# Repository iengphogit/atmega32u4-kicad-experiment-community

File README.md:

# ATmega32U4 Arduino-Compatible USB-C Bluetooth Module

This KiCad project is a learning-focused starter design for an ATmega32U4-based Arduino-compatible module. It includes a schematic-first design flow, a PCB layout with placed footprints, a custom module footprint example, and notes for using KiCad MCP automation.

## Repository Scope

This repository contains KiCad project files, learning notes, and usage examples
for KiCad MCP. It does not vendor or mirror the full `kicad-mcp` npm package
source code.

For the KiCad MCP source code, package launcher, Codex skill, and KiCad action
plugin implementation, use:

```text
https://github.com/iengphogit/kicad-mcp
```

## What This Project Contains

- ATmega32U4 microcontroller schematic connectivity
- USB Type-C female connector wiring
- HC-05 / HM-10 compatible Bluetooth header
- Arduino-style 2.54 mm headers
- Reset circuit
- 16 MHz crystal circuit
- USB-C CC1/CC2 5.1k pull-down support
- Power and decoupling capacitors
- PCB footprints placed in PCB Editor
- Rectangular board outline on `Edge.Cuts`
- Custom example footprint library in `TestDemo.pretty`

## Included KiCad Projects

This community repo now contains multiple KiCad learning projects:

- `TestDemo.kicad_pro` - ATmega32U4 Arduino-compatible USB-C Bluetooth module
- `Card_Reader_Adapter/Card_Reader_Adapter.kicad_pro` - smart-card reader adapter with ISO 7816 contacts and RJ45 connector

## Project Files

```text
TestDemo.kicad_pro     KiCad project file
TestDemo.kicad_sch     Main schematic
TestDemo.kicad_pcb     PCB layout
fp-lib-table           Project footprint library table
TestDemo.pretty/       Project-local footprint library
KICAD_STARTUP_SCENARIO.md  Learning notes and startup scenario
```

Generated reports:

```text
TestDemo.erc.json          ERC report for schematic
TestDemo.validate-drc.json DRC report for PCB
```

Backup files are also present because KiCad MCP write operations were run with backups enabled.

## Recommended Learning Order

Start with **Schematic Editor**, not Footprint Editor.

1. Open the KiCad project.
2. Learn symbols, wires, labels, and nets in Schematic Editor.
3. Assign footprints to schematic symbols.
4. Update PCB from schematic.
5. Place and route footprints in PCB Editor.
6. Use Footprint Editor only when creating or editing one reusable physical footprint.
7. Run ERC and DRC before manufacturing output.

Important distinction:

```text
Symbol          Electrical part in schematic
Footprint       Physical pad pattern for one part
Net             Named electrical connection
PCB layout      Physical board with placed footprints and routed tracks
```

## Opening The Project In KiCad

1. Install KiCad 9.x or newer.
2. Open KiCad.
3. Open this project file:

```text
TestDemo.kicad_pro
```

From the Project Manager:

- Open **Schematic Editor** to see the ATmega32U4 circuit.
- Open **PCB Editor** to see the placed PCB footprints and board outline.
- Open **Footprint Editor** only to inspect project-local custom footprints.

## Viewing The Schematic

Open:

```text
TestDemo.kicad_sch
```

The schematic includes:

- `U1`: ATmega32U4-A
- `J1`: USB-C receptacle
- `J2`: Arduino-compatible digital header
- `J3`: power, analog, and USB breakout header
- `J4`: HC-05 / HM-10 Bluetooth header
- `R1`, `R2`: 5.1k USB-C CC pull-down resistors
- `R3`: reset pull-up
- `SW1`: reset switch
- `Y1`: 16 MHz crystal
- `C1` to `C8`: decoupling, UCAP, AREF, 5V bulk, and crystal load capacitors

Key net labels:

```text
5V
VCC
GND
RESET
USB_DP
USB_DM
CC1
CC2
TX0
RX1
D2_SDA
D3_SCL
D4 to D10
A0 to A5
BT_STATE
BT_EN_KEY
```

## Viewing The PCB

Open:

```text
TestDemo.kicad_pcb
```

The PCB contains placed footprints for:

- ATmega32U4 TQFP-44
- USB-C connector
- Digital, analog, power, USB, and Bluetooth headers
- Resistors and capacitors
- Crystal
- Reset switch
- Four M2 mounting holes
- Board outline on `Edge.Cuts`

If footprints are visible in PCB Editor but not in Footprint Editor, that is normal. PCB Editor shows the board. Footprint Editor shows only one reusable footprint from a library.

## Viewing The Custom Footprint

This project also includes a project-local footprint library:

```text
TestDemo.pretty/
```

It is registered by:

```text
fp-lib-table
```

The custom footprint file is:

```text
TestDemo.pretty/ATmega32U4_Arduino_USB-C_BT_Module.kicad_mod
```

To view it in Footprint Editor:

1. Open `TestDemo.kicad_pro` in KiCad.
2. Open **Footprint Editor**.
3. Select the `TestDemo` library from the library tree.
4. Open `ATmega32U4_Arduino_USB-C_BT_Module`.

If the Footprint Editor appears empty, make sure the project was opened from `TestDemo.kicad_pro`, not by opening a single `.kicad_mod` file directly.

## USB-C Connectivity

The schematic uses these USB-C connections:

```text
VBUS   -> 5V
GND    -> GND
Shield -> GND
D+     -> USB_DP
D-     -> USB_DM
CC1    -> 5.1k pull-down to GND
CC2    -> 5.1k pull-down to GND
SBU1   -> no connect
SBU2   -> no connect
```

## Bluetooth Header

The Bluetooth header is intended for HC-05 / HM-10 style modules:

```text
Pin 1  VCC
Pin 2  GND
Pin 3  RX1
Pin 4  TX0
Pin 5  BT_STATE
Pin 6  BT_EN_KEY
```

Check the exact TX/RX direction for your module before manufacturing. Many Bluetooth modules label pins from the module perspective, so MCU `TX0` normally connects to module `RX`, and MCU `RX1` normally connects to module `TX`.

## KiCad Checks

Run ERC from KiCad:

```text
Schematic Editor > Inspect > Electrical Rules Checker
```

Run DRC from KiCad:

```text
PCB Editor > Inspect > Design Rules Checker
```

Command-line examples on macOS with KiCad installed in `/Applications`:

```sh
/Applications/KiCad/KiCad.app/Contents/MacOS/kicad-cli sch erc \
  --output TestDemo.erc.json \
  --format json \
  TestDemo.kicad_sch

/Applications/KiCad/KiCad.app/Contents/MacOS/kicad-cli pcb drc \
  --output TestDemo.validate-drc.json \
  --format json \
  TestDemo.kicad_pcb
```

## Update PCB From Schematic

After editing the schematic, update the PCB from KiCad GUI:

```text
PCB Editor > Tools > Update PCB from Schematic
```

This step synchronizes footprints, nets, and ratsnest connections from the schematic into the PCB.

Note: the installed `kicad-cli` can run ERC, DRC, exports, and reports, but it does not expose full GUI-equivalent **Update PCB from Schematic** for this setup. Use the KiCad GUI for that step.

## Install KiCad MCP With npm

KiCad MCP lets AI tools inspect and automate KiCad projects. The npm package provides a Node.js launcher for the KiCad MCP server.

Requirements:

- Node.js and npm
- Python 3.10 or newer
- KiCad installed
- `kicad-cli` available or passed with `--kicad-cli`

Check npm package information:

```sh
npm view kicad-mcp version description bin
```

Run KiCad MCP directly with `npx`:

```sh
npx -y kicad-mcp@latest
```

By default this runs MCP over stdio, which is the normal mode for MCP clients.

Run setup explicitly:

```sh
npx -y kicad-mcp@latest --setup
```

Run local HTTP mode:

```sh
npx -y kicad-mcp@latest --http --host 127.0.0.1 --port 8765
```

The HTTP MCP endpoint is:

```text
http://127.0.0.1:8765/mcp
```

Keep the host set to `127.0.0.1` unless you add proper authentication.

Install globally with npm:

```sh
npm install -g kicad-mcp
```

Then run:

```sh
kicad-mcp --help
kicad-mcp --stdio
kicad-mcp --http --host 127.0.0.1 --port 8765
```

Useful options:

```sh
kicad-mcp --setup
kicad-mcp --install-codex-skill
kicad-mcp --python /path/to/python3
kicad-mcp --venv /path/to/venv
kicad-mcp --kicad-cli /Applications/KiCad/KiCad.app/Contents/MacOS/kicad-cli
```

## MCP Client Configuration

Example MCP client configuration using `npx`:

```json
{
  "mcpServers": {
    "kicad": {
      "command": "npx",
      "args": ["-y", "kicad-mcp@latest"]
    }
  }
}
```

Example HTTP startup command:

```sh
npx -y kicad-mcp@latest --http --host 127.0.0.1 --port 8765 \
  --kicad-cli /Applications/KiCad/KiCad.app/Contents/MacOS/kicad-cli
```

## Install The Codex Skill

The npm package can install the bundled Codex skill:

```sh
npx -y kicad-mcp@latest --install-codex-skill
```

This installs the skill to:

```text
~/.codex/skills/kicad-mcp
```

If Codex uses a custom home directory, install to that directory instead:

```sh
CODEX_HOME="/path/to/codex-home" npx -y kicad-mcp@latest --install-codex-skill
```

Use the actual Codex home directory for your environment as `CODEX_HOME`.

After restarting Codex, use:

```text
$kicad-mcp
```

Run Codex from this repository root so the skill can inspect `TestDemo.kicad_pro`, `TestDemo.kicad_sch`, and `TestDemo.kicad_pcb`.

Example prompt:

```text
Use $kicad-mcp to inspect this KiCad project, run ERC/DRC, and report the current schematic and board status.
```

## KiCad MCP Safe Workflow

Recommended automation order:

1. Find project files: `.kicad_pro`, `.kicad_sch`, `.kicad_pcb`.
2. Run read-only checks first: project summary, schematic statistics, board statistics.
3. Before write operations, run `dry_run=true` when supported.
4. Keep `create_backup=true` for edits.
5. After schematic edits, run ERC.
6. After PCB edits, run DRC.
7. Report changed files, generated reports, and backup paths.

Useful KiCad MCP task examples:

```text
kicad_find_project_files
kicad_project_summary
kicad_schematic_statistics
kicad_list_schematic_symbols
kicad_list_schematic_nets
kicad_run_erc
kicad_board_statistics
kicad_list_board_footprints
kicad_validate_board
kicad_run_drc
kicad_export_bom
kicad_export_gerbers
kicad_export_drill_files
```

## KiCad GUI Bridge

Some KiCad MCP GUI actions require the PCB Editor bridge.

To use it:

1. Open KiCad PCB Editor.
2. Open the target board.
3. Run:

```text
Tools > External Plugins > KiCad AI MCP
```

The GUI bridge normally listens locally at:

```text
http://127.0.0.1:8766/status
```

If the bridge is not running, MCP can still edit saved KiCad files, but live GUI actions such as selecting, zooming, and moving visible PCB items will not work.

## Suggested Beginner Workflow For This Project

1. Open `TestDemo.kicad_pro`.
2. Open Schematic Editor and study the net labels.
3. Run ERC.
4. Open PCB Editor.
5. Run **Update PCB from Schematic**.
6. Inspect the placed footprints.
7. Route `USB_DP` and `USB_DM` carefully as a short pair.
8. Route power and ground.
9. Add a ground zone.
10. Run DRC.
11. Generate fabrication outputs only after DRC is clean.

## Manufacturing Outputs

When the board is ready, generate files from PCB Editor:

```text
File > Fabrication Outputs > Gerbers
File > Fabrication Outputs > Drill Files
File > Fabrication Outputs > Component Placement
```

You can also use KiCad MCP or `kicad-cli` for exports after the board is finalized.

## Notes

- This is a starter learning design, not a certified Arduino product.
- Review the ATmega32U4 datasheet before manufacturing.
- Confirm USB-C footprint compatibility with the exact connector part number.
- Confirm Bluetooth module pin direction and voltage level requirements.
- Route USB data lines carefully and keep them short.
- Add or tune PCB design rules before ordering boards.

## Credits And Contact

Created by Ieng Pho.

- GitHub: [iengphogit](https://github.com/iengphogit)
- Facebook: [ieng.pho](https://www.facebook.com/ieng.pho/)
- LinkedIn: [Ieng Pho](https://www.linkedin.com/in/ieng-pho-7a4328189/)
- Email: [iengpho@gmail.com](mailto:iengpho@gmail.com)

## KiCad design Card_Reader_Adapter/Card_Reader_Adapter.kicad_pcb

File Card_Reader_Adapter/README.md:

# Card Reader Adapter KiCad Project

KiCad project for a smart-card reader adapter inspired by `nkinder/smart-card-removinator`.

The PCB uses ISO 7816 contact pads on the card-reader side and an RJ45 connector on the cable side. The routed core nets are:

- RJ45 pin 1 -> AUX1
- RJ45 pin 2 -> I/O
- RJ45 pin 3 -> CLK
- RJ45 pin 4 -> AUX2
- RJ45 pin 5 -> RST
- RJ45 pin 6 -> VPP
- RJ45 pin 7 -> GND
- RJ45 pin 8 -> VCC

Important fabrication note: order this board as **0.031 inch / 0.8 mm PCB thickness** so it can fit into a smart-card reader slot.

Files:

- `Card_Reader_Adapter.kicad_pro` - KiCad project
- `Card_Reader_Adapter.kicad_sch` - visible schematic with U1 smart-card contacts and J1 RJ45 mapping
- `Card_Reader_Adapter.kicad_sym` / `sym-lib-table` - project-local schematic symbols
- `Card_Reader_Adapter.kicad_pcb` - routed PCB layout
- `Card_Reader_Adapter.pretty/` - project-local footprints
- `reference/` - original SVG schematic and Gerber files from the public reference repository

Validation run with KiCad 9.0.4:

- ERC: 0 violations
- DRC: 0 violations, 0 unconnected items

R1 is included as an optional RJ45 LED resistor footprint. The smart-card adapter core is the eight ISO 7816 signal routes listed above.

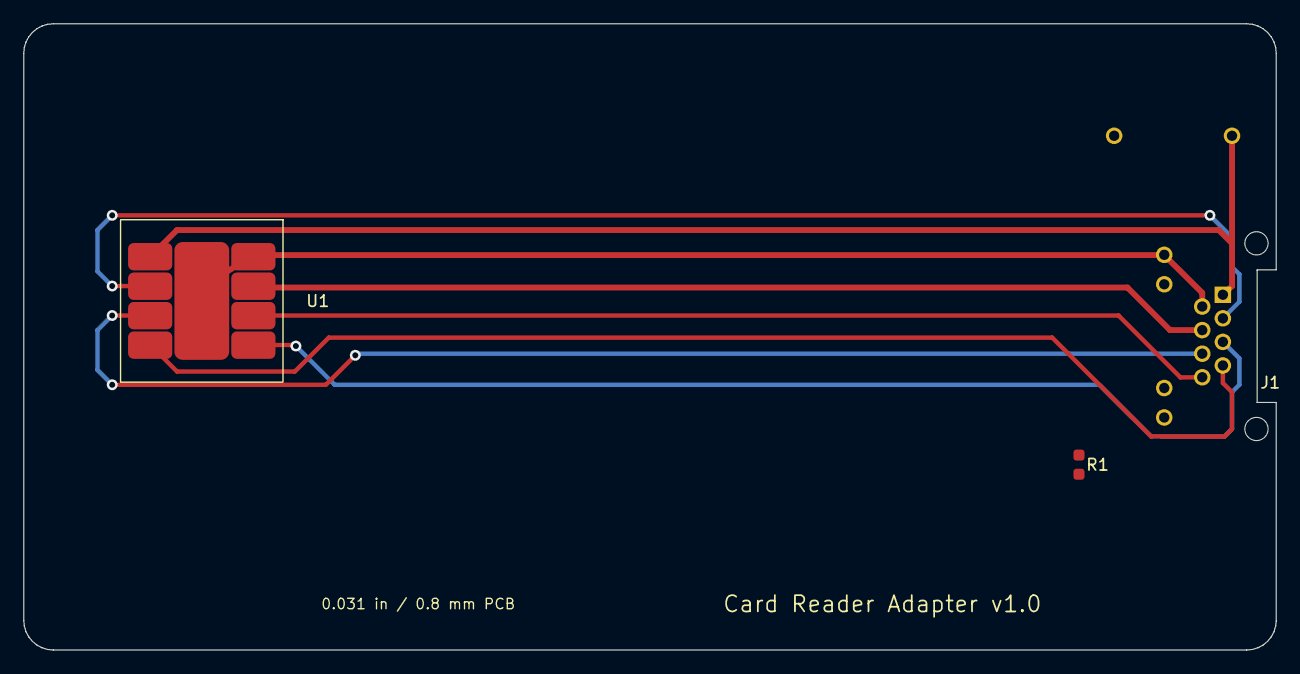
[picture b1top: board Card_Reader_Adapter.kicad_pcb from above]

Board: 2 copper layers, 108.0 x 54.0 mm, 3 parts (0 on the bottom side), 8 nets.

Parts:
J1: Amphenol_RJ45_LED; RJ45_12P_Amphenol_LED_Adapter
R1: 330ohm; R_0603_1608Metric
U1: Smart_Card_Contacts; Smart_Card_ISO7816_Adapter_Contacts

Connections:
/AUX1: J1.1, J1.AUX1_TAP, U1.AUX1
/AUX2: J1.4, U1.AUX2
/CLK: J1.3, U1.CLK
/GND: J1.7, U1.GND
/IO: J1.2, J1.9, U1.CD, U1.IO
/RST: J1.5, U1.RST
/VCC: J1.8, U1.VCC
/VPP: J1.6, U1.VPP

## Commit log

2026-05-22 Add ATmega32U4 KiCad community project
2026-05-22 Add creator credits and contact links
2026-05-22 Update KiCad MCP npm install command
2026-05-26 Clarify KiCad MCP Codex skill install
2026-05-26 Document repository scope
